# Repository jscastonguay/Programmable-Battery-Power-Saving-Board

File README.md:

# Programmable-Battery-Power-Saving-Board
Board to save battery life using a RTC to disconnect the battery power from the load.

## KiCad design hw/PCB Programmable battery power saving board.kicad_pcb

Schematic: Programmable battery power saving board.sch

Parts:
BT1: Battery; batter3V
C1, C2, C3: 1u; CP_Radial_D5.0mm_P2.00mm
P1: 277-9143; TerminalBlock_Pheonix_PT-3.5mm_9pol
P2: power_in; AK300-2
P3: power_out; AK300-2
Q1, Q2, Q3, Q5: TN0606N3-G; TO-92_Inline_Narrow_Oval
Q4: IPP45P03P4L-11; TO-220_Vertical
Q6: LP0701N3-G; TO-92_Inline_Narrow_Oval
R1, R2, R3, R4: 470k; R_Axial_DIN0207_L6.3mm_D2.5mm_P7.62mm_Horizontal
R5, R9, R10: 10k; R_Axial_DIN0207_L6.3mm_D2.5mm_P7.62mm_Horizontal
R6, R7: 330k; R_Axial_DIN0207_L6.3mm_D2.5mm_P7.62mm_Horizontal
R8: 30k; R_Axial_DIN0207_L6.3mm_D2.5mm_P7.62mm_Horizontal
SW1, SW2: SW_PUSH; sw_push
U11: DS3231S; SOIC-16W_7.5x10.3mm_Pitch1.27mm

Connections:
GND: BT1.2, C1.2, C2.1, C3.2, P1.8, P2.2, P3.2, Q1.1 (S), Q2.1 (S), Q3.1 (S), Q5.1 (S), R3.2, R6.2, R9.2, SW2.2, U11.5 (N.C.), U11.6 (N.C.), U11.7 (N.C.), U11.8 (N.C.), U11.9 (N.C.), U11.10 (N.C.), U11.11 (N.C.), U11.12 (N.C.), U11.13 (GND)
unnamed: BT1.1, C1.1, R4.1, U11.14 (VBAT)
unnamed: C2.2, U11.2 (Vcc)
unnamed: C3.1, P1.5, R8.2, R9.1
unnamed: P1.2, U11.16 (SCL)
unnamed: P1.3, U11.15 (SDA)
unnamed: P1.4, U11.4 (RST)
unnamed: P1.6, Q5.2 (G), R6.1
unnamed: P1.7, Q3.2 (G), R3.1
unnamed: P1.9, R10.2, SW2.1
unnamed: P2.1, Q4.3 (D), Q6.3 (D), R1.1, R2.1, R7.1, SW1.1
unnamed: P3.1, Q4.2 (S), SW1.2
unnamed: Q1.2 (G), R4.2, U11.3 (INT/SQW)
unnamed: Q1.3 (D), Q2.2 (G), R1.2
unnamed: Q2.3 (D), Q3.3 (D), Q4.1 (G), R2.2
unnamed: Q5.3 (D), Q6.2 (G), R7.2
unnamed: Q6.1 (S), R8.1
unnamed: R5.2, U11.1 (32kHz)
VCC: P1.1, R5.1, R10.1

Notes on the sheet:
Pinout P1 (1) Vcc from the controler (3.3V, 5V) (2) SCL from the controler (3) SDA from the controler (4) RST from the controler (5) Valim - voltage divisor per 4 (6) Measure Valim? from an external source (7) Power controler (8) GND from the controler (9) maintenance
Alimentation from the external power source
RTC (real-time clock) module
Voltage divisor for the measure of Valim
Mode selection: normal or maintenance

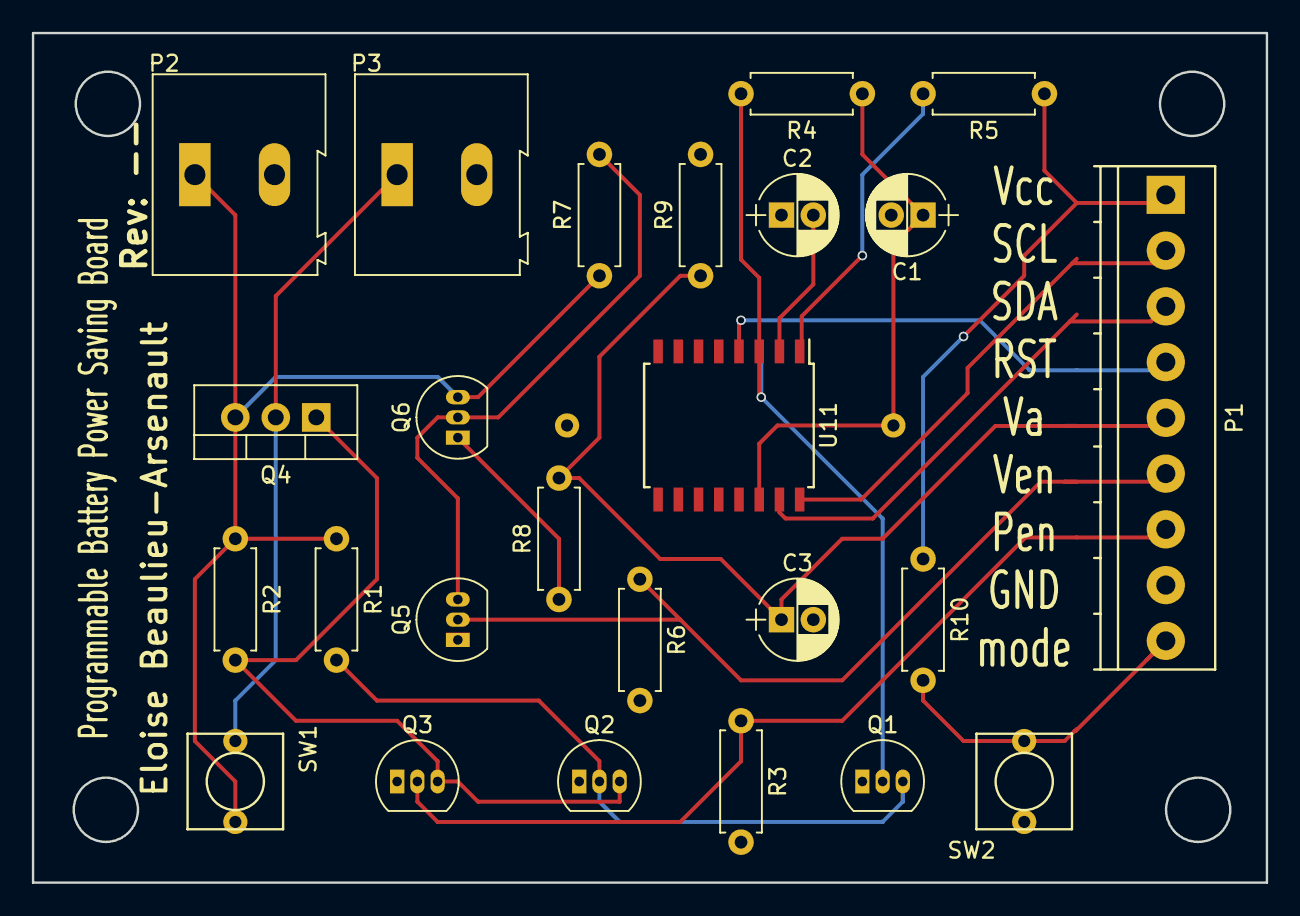
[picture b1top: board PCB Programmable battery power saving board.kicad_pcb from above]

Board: 2 copper layers, 77.5 x 53.3 mm, 26 parts (1 on the bottom side), 19 nets.

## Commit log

2017-05-10 During dev.
2017-05-14 Last changed from Eloise

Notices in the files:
hw/PCB Programmable battery power saving board.kicad_pcb:
Copyright 2017 Eloïse Beaulieu-Arsenault
hw/Programmable battery power saving board.sch:
Copyright 2017 Éloïse Beaulieu-Arsenault
